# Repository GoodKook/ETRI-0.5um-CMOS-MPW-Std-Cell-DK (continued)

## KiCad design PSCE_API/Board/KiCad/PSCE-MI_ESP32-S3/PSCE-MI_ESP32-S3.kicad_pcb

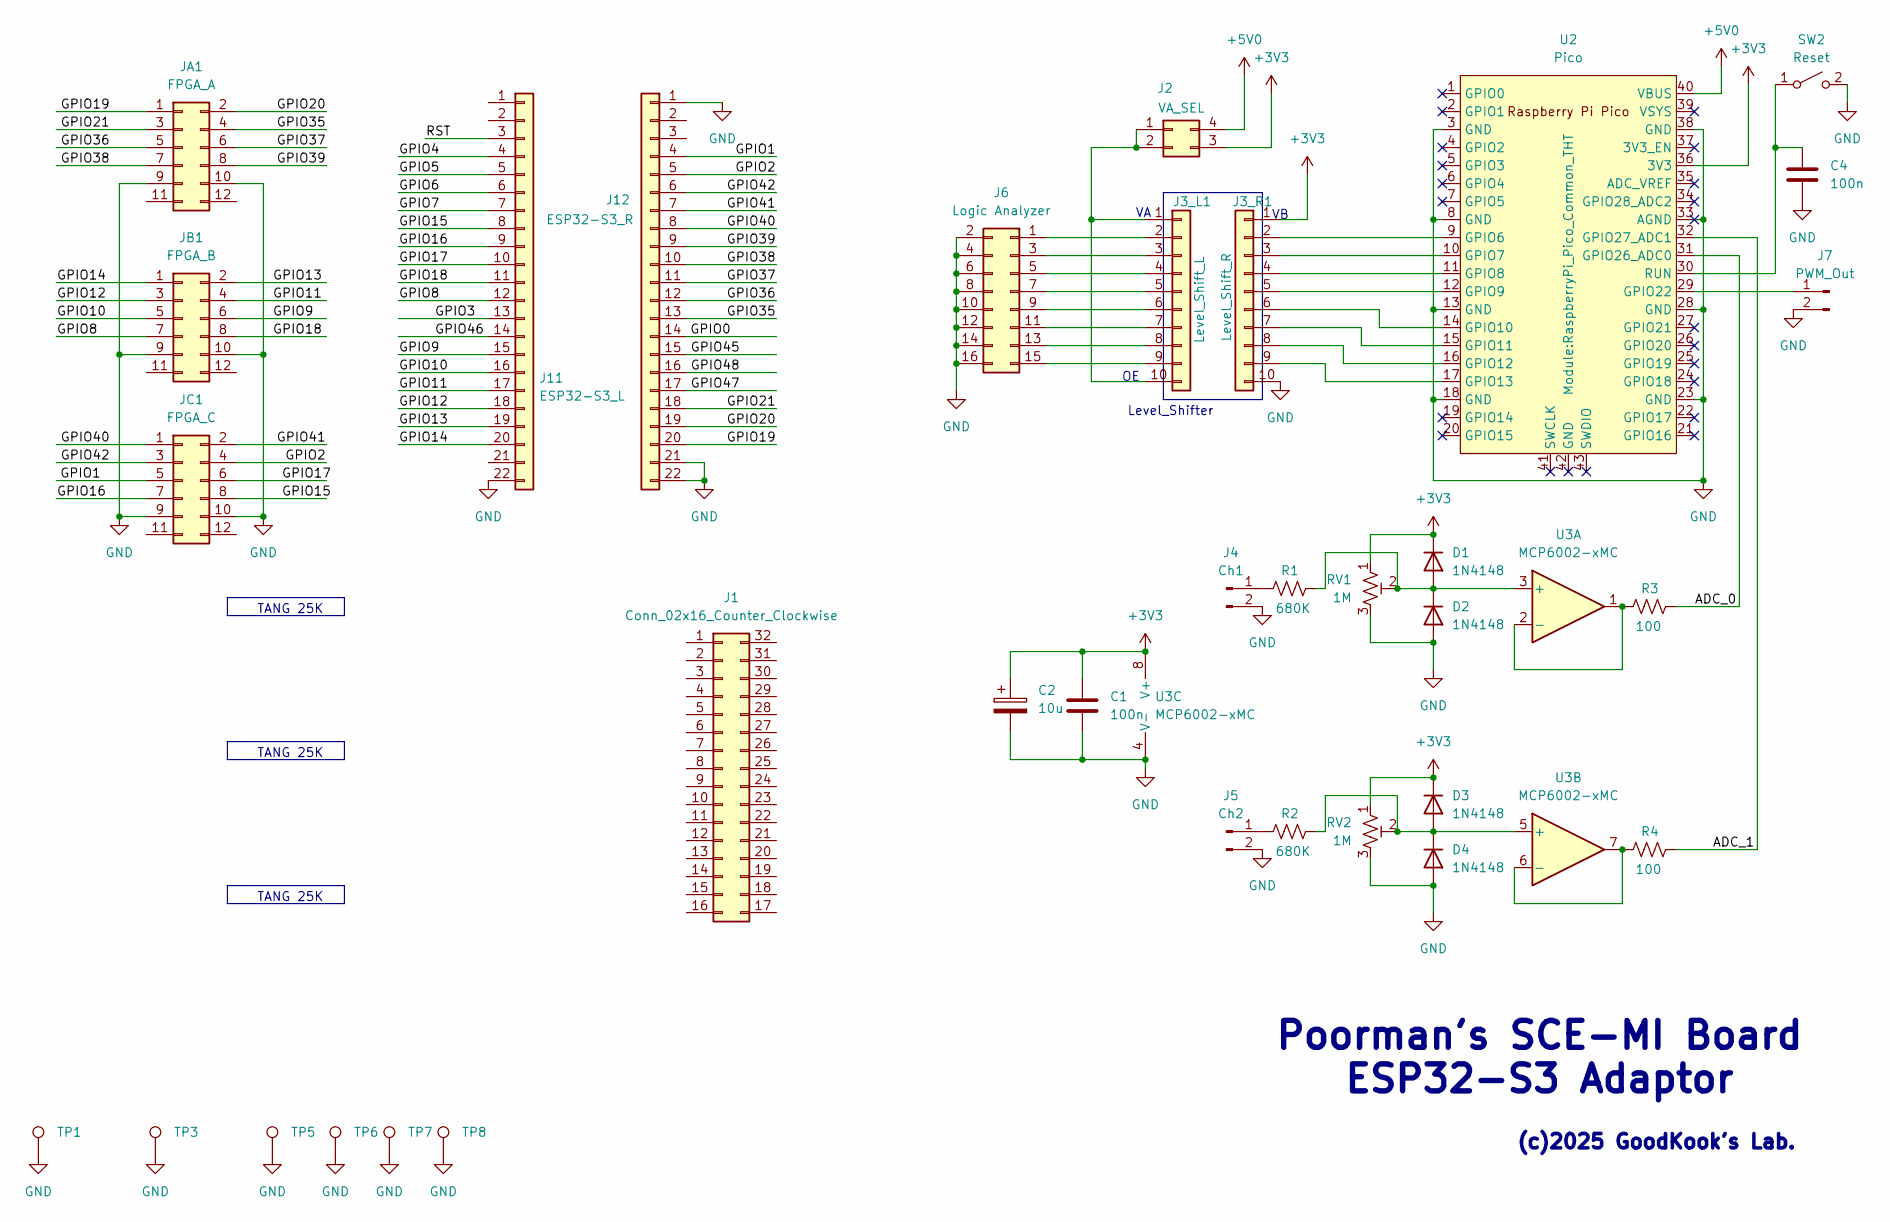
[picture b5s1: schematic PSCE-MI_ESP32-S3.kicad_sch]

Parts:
C1, C4: 100n; C_Disc_D3.8mm_W2.6mm_P2.50mm
C2: 10u; CP_Radial_Tantal_D9.0mm_P2.50mm
D1, D2, D3, D4: 1N4148; D_DO-35_SOD27_P7.62mm_Horizontal
J1: Conn_02x16_Counter_Clockwise; PinHeader_2x16_P2.54mm_Vertical
J2: VA_SEL; PinHeader_2x02_P2.54mm_Vertical
J3_L1: Level_Shift_L; PinHeader_1x10_P2.54mm_Vertical
J3_R1: Level_Shift_R; PinHeader_1x10_P2.54mm_Vertical
J4: Ch1; PinHeader_2x01_P2.54mm_Vertical
J5: Ch2; PinHeader_2x01_P2.54mm_Vertical
J6: Logic Analyzer; PinHeader_2x08_P2.54mm_Vertical
J7: PWM_Out; PinHeader_2x01_P2.54mm_Vertical
J11: ESP32-S3_L; PinHeader_1x22_P2.54mm_Vertical
J12: ESP32-S3_R; PinHeader_1x22_P2.54mm_Vertical
JA1: FPGA_A; PinHeader_2x06_P2.54mm_Vertical
JB1: FPGA_B; PinHeader_2x06_P2.54mm_Vertical
JC1: FPGA_C; PinHeader_2x06_P2.54mm_Vertical
R1, R2: 680K; R_Axial_DIN0204_L3.6mm_D1.6mm_P7.62mm_Horizontal
R3, R4: 100; R_Axial_DIN0204_L3.6mm_D1.6mm_P7.62mm_Horizontal
RV1, RV2: 1M; Potentiometer_Runtron_RM-065_Vertical
SW2: Reset; SW_PUSH_6mm_H5mm
TP1, TP3, TP5, TP6, TP7, TP8: Mounting Hole; MountingHole_3.2mm_M3
U2: Pico; RaspberryPi_Pico_Common_THT
U3: MCP6002-xMC; DIP-8_W10.16mm_LongPads

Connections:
+3V3: C1.1, C2.1, D1.1 (K), D3.1 (K), J2.3, J3_R1.1, RV1.1, RV2.1, U2.36 (3V3), U3.8 (V+)
+5V0: J2.4, U2.40 (VBUS)
/ADC_0: R3.1, U2.31 (GPIO26_ADC0)
/ADC_1: R4.1, U2.32 (GPIO27_ADC1)
/GPIO0: J12.14
/GPIO1: J12.4, JC1.5
/GPIO2: J12.5, JC1.4
/GPIO3: J11.13
/GPIO4: J11.4
/GPIO5: J11.5
/GPIO6: J11.6
/GPIO7: J11.7
/GPIO8: J11.12, JB1.7
/GPIO9: J11.15, JB1.6
/GPIO10: J11.16, JB1.5
/GPIO11: J11.17, JB1.4
/GPIO12: J11.18, JB1.3
/GPIO13: J11.19, JB1.2
/GPIO14: J11.20, JB1.1
/GPIO15: J11.8, JC1.8
/GPIO16: J11.9, JC1.7
/GPIO17: J11.10, JC1.6
/GPIO18: J11.11, JB1.8
/GPIO19: J12.20, JA1.1
/GPIO20: J12.19, JA1.2
/GPIO21: J12.18, JA1.3
/GPIO35: J12.13, JA1.4
/GPIO36: J12.12, JA1.5
/GPIO37: J12.11, JA1.6
/GPIO38: J12.10, JA1.7
/GPIO39: J12.9, JA1.8
/GPIO40: J12.8, JC1.1
/GPIO41: J12.7, JC1.2
/GPIO42: J12.6, JC1.3
/GPIO45: J12.15
/GPIO46: J11.14
/GPIO47: J12.17
/GPIO48: J12.16
/RST: J11.3
GND: C1.2, C2.2, C4.2, D2.2 (A), D4.2 (A), J3_R1.10, J4.2, J5.2, J6.2, J6.4, J6.6, J6.8, J6.10, J6.12, J6.14, J6.16, J7.2, J11.22, J12.1, J12.21, J12.22, JA1.9, JA1.10, JB1.9, JB1.10, JC1.9, JC1.10, RV1.3, RV2.3, SW2.2 (B), TP1.1, TP3.1, TP5.1, TP6.1, TP7.1, TP8.1, U2.3 (GND), U2.8 (GND), U2.13 (GND), U2.18 (GND), U2.23 (GND), U2.28 (GND), U2.33 (AGND), U2.38 (GND), U3.4 (V-), U3.9 (V-)
unnamed: D1.2 (A), D2.1 (K), R1.1, RV1.2, U3.3 (+)
unnamed: D3.2 (A), D4.1 (K), R2.1, RV2.2, U3.5 (+)
unnamed: J2.1, J2.2, J3_L1.1, J3_L1.10
unnamed: J3_L1.2, J6.1
unnamed: J3_L1.3, J6.3
unnamed: J3_L1.4, J6.5
unnamed: J3_L1.5, J6.7
unnamed: J3_L1.6, J6.9
unnamed: J3_L1.7, J6.11
unnamed: J3_L1.8, J6.13
unnamed: J3_L1.9, J6.15
unnamed: J3_R1.2, U2.9 (GPIO6)
unnamed: J3_R1.3, U2.10 (GPIO7)
unnamed: J3_R1.4, U2.11 (GPIO8)
unnamed: J3_R1.5, U2.12 (GPIO9)
unnamed: J3_R1.6, U2.14 (GPIO10)
unnamed: J3_R1.7, U2.15 (GPIO11)
unnamed: J3_R1.8, U2.16 (GPIO12)
unnamed: J3_R1.9, U2.17 (GPIO13)
unnamed: J4.1, R1.2
unnamed: J5.1, R2.2
unnamed: J7.1, U2.29 (GPIO22)
unnamed: C4.1, SW2.1 (A), U2.30 (RUN)
unnamed: R3.2, U3.1, U3.2 (-)
unnamed: R4.2, U3.6 (-), U3.7

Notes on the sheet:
Poorman's SCE-MI Board ESP32-S3 Adaptor
TANG 25K
(c)2025 GoodKook's Lab.
Level_Shifter

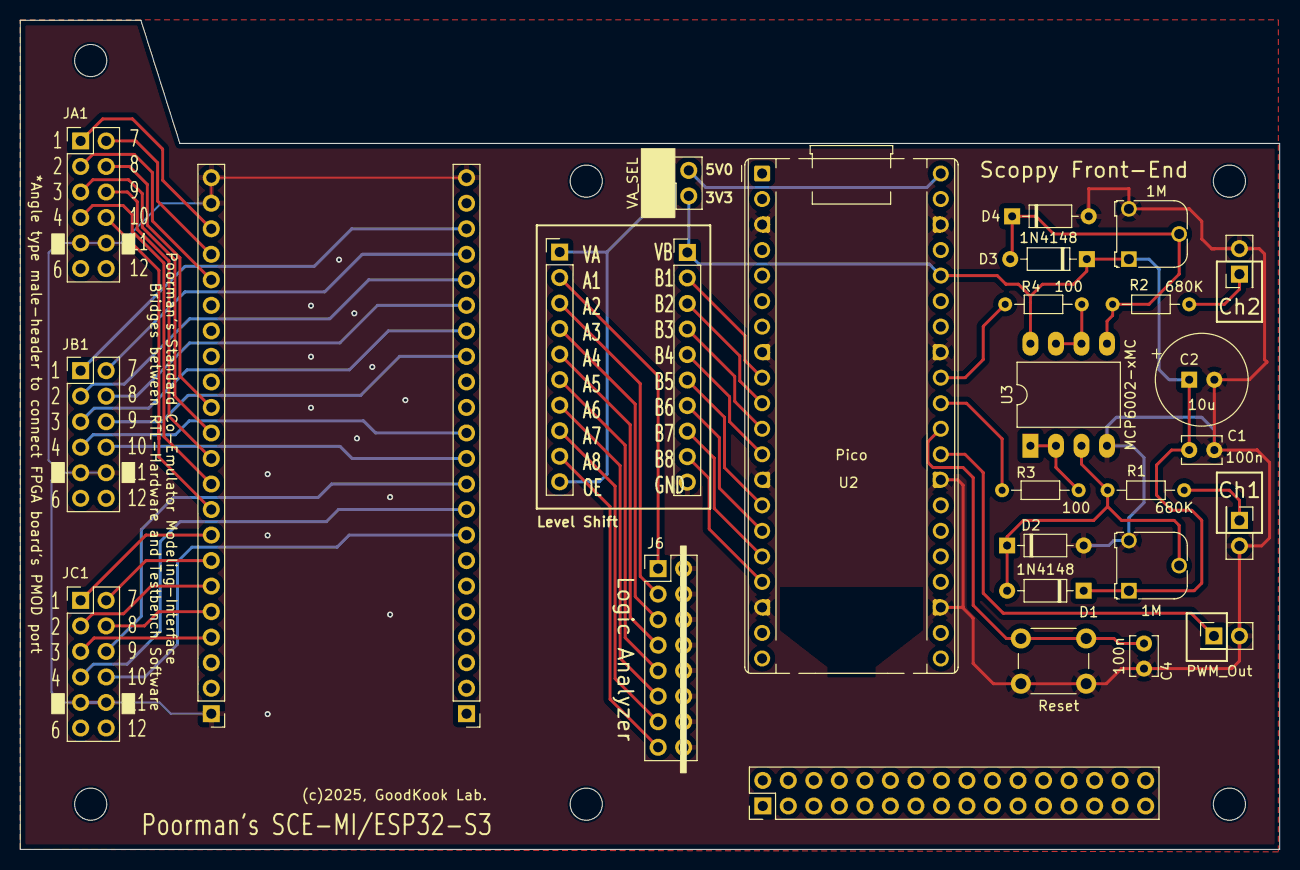
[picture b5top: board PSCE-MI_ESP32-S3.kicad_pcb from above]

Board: 2 copper layers, 125.3 x 82.5 mm, 35 parts (0 on the bottom side), 54 nets.

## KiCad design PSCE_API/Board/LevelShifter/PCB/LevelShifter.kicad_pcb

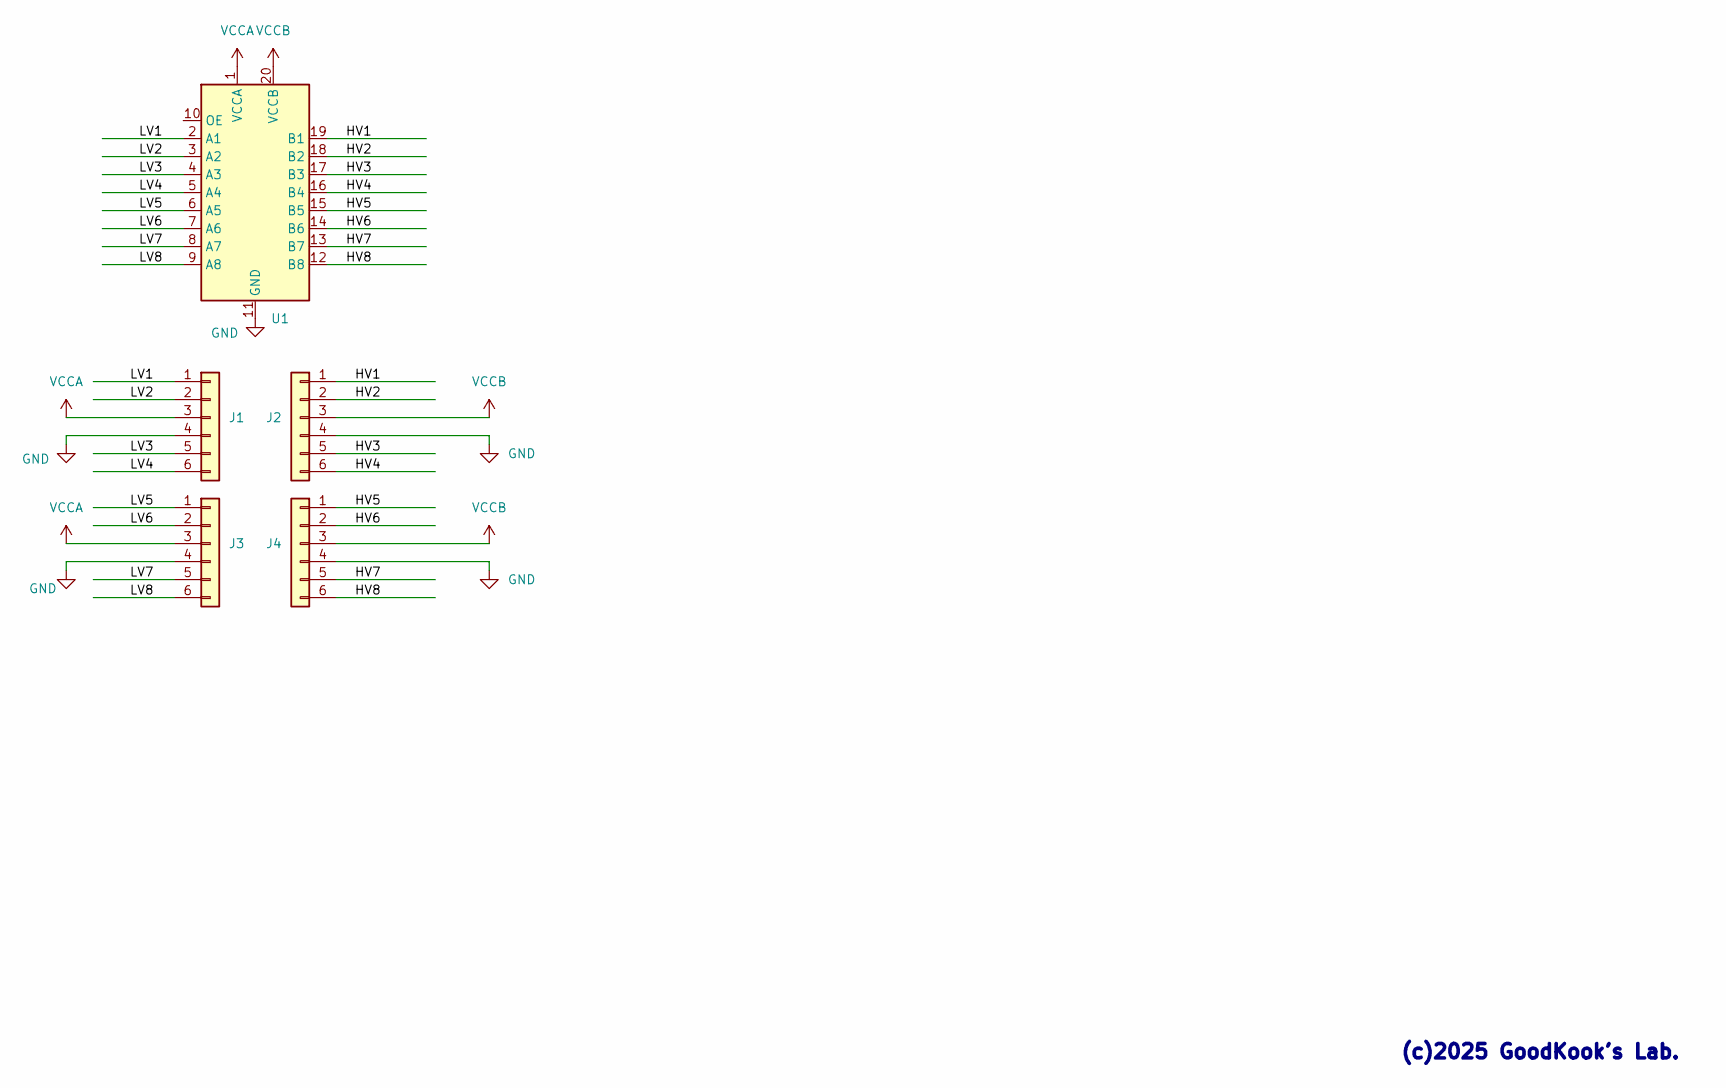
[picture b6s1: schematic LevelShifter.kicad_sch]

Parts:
J1, J2, J3, J4: Conn_01x06; PinHeader_1x06_P2.54mm_Vertical
U1: Level_Shifter_Module_HW-221

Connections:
/HV1: J2.1, U1.19 (B1)
/HV2: J2.2, U1.18 (B2)
/HV3: J2.5, U1.17 (B3)
/HV4: J2.6, U1.16 (B4)
/HV5: J4.1, U1.15 (B5)
/HV6: J4.2, U1.14 (B6)
/HV7: J4.5, U1.13 (B7)
/HV8: J4.6, U1.12 (B8)
/LV1: J1.1, U1.2 (A1)
/LV2: J1.2, U1.3 (A2)
/LV3: J1.5, U1.4 (A3)
/LV4: J1.6, U1.5 (A4)
/LV5: J3.1, U1.6 (A5)
/LV6: J3.2, U1.7 (A6)
/LV7: J3.5, U1.8 (A7)
/LV8: J3.6, U1.9 (A8)
GND: J1.4, J2.4, J3.4, J4.4, U1.11 (GND)
VCCA: J1.3, J3.3, U1.1 (VCCA)
VCCB: J2.3, J4.3, U1.20 (VCCB)

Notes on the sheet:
(c)2025 GoodKook's Lab.

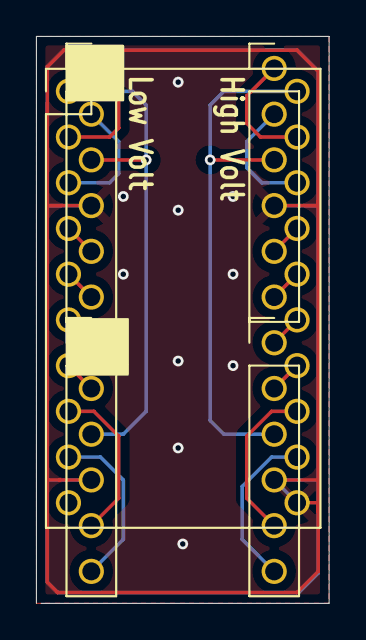
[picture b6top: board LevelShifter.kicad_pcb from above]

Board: 2 copper layers, 16.3 x 31.5 mm, 5 parts (0 on the bottom side), 19 nets.
